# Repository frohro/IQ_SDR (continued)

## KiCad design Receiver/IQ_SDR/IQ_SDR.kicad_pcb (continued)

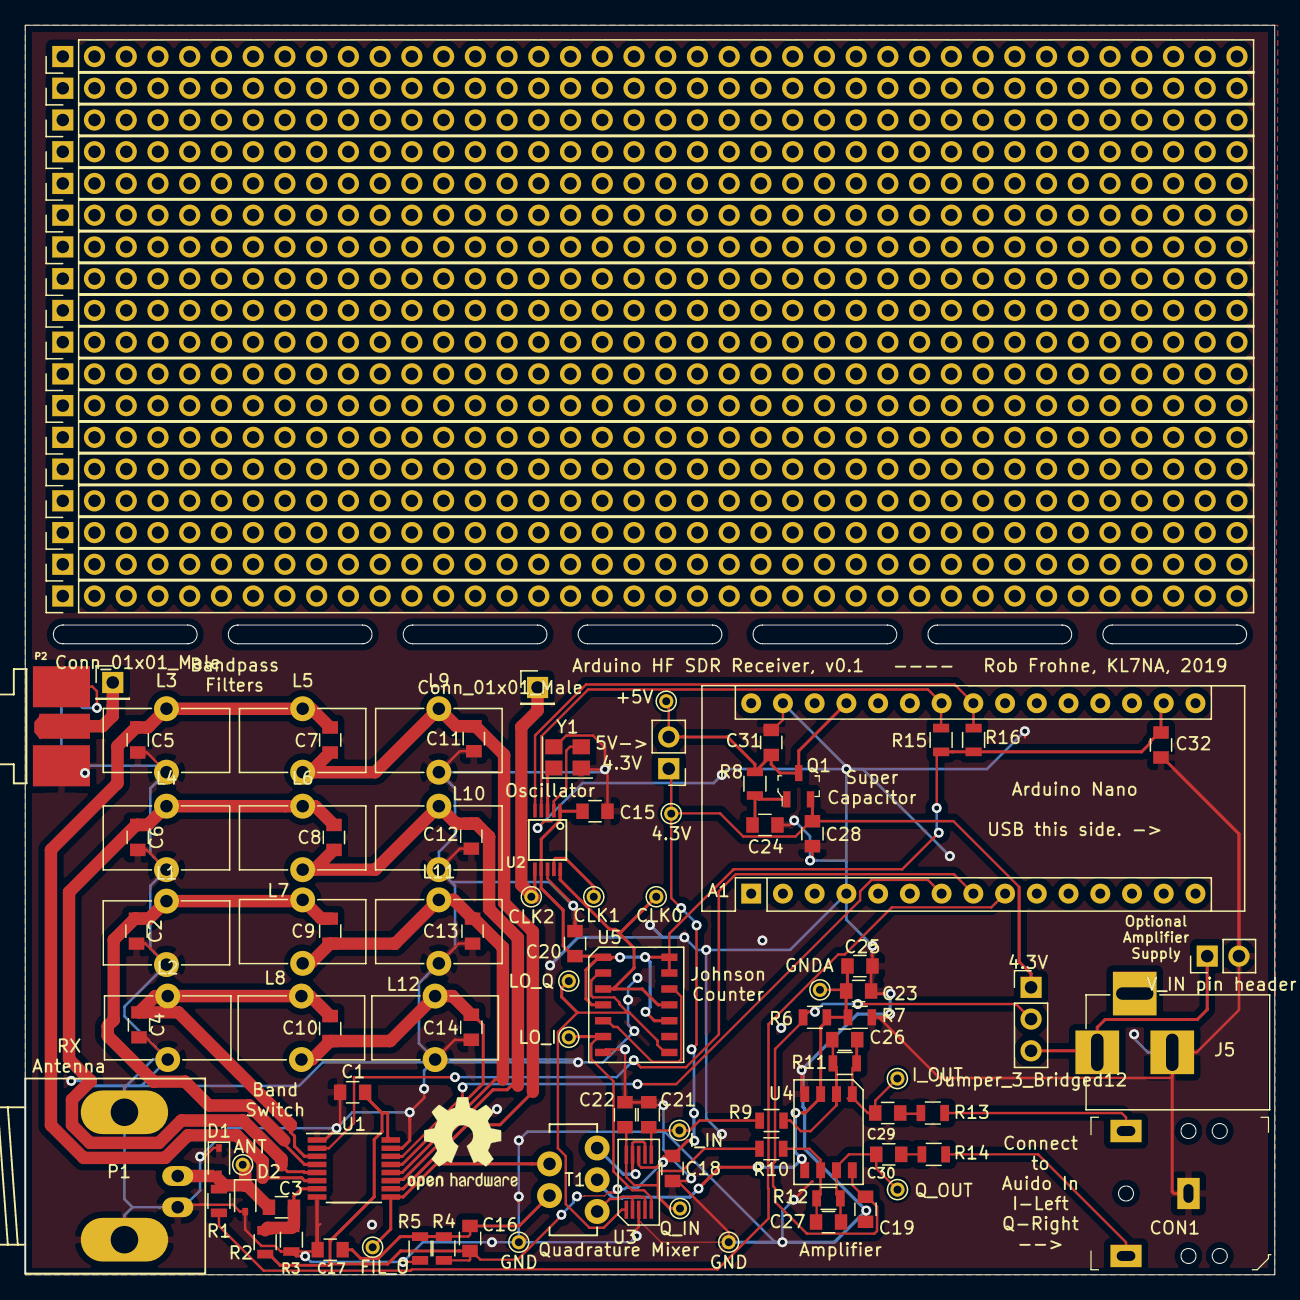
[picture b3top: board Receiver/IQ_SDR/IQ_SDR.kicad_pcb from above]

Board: 2 copper layers, 100.0 x 100.0 mm, 96 parts (0 on the bottom side), 46 nets.

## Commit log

2019-06-06 First commit.
2019-06-07 Fixed schematic issues in Receiver and Transceiver
2019-06-27 Started PI filters.
2019-06-27 Added files .net and .pdf to Receiver
2019-06-28 A little clean up on the schematic
2019-06-28 More cleanup of schematic
2019-07-05 Changes to power and perhaps a better op amp...
2019-07-12 Added PCB.
2019-07-12 ...added the other new kicad files.
2019-09-08 Add inductor/transformer details. Change U1 package type. (Maybe should change the IC as we did in rev 0.1.)
2019-12-15 Added torroid data.
2019-12-17 saving changes so I can merge from hamshack.
2019-12-17 A few more schematic notes from shop.
2019-12-17 Added in changes from the shop after failed merge.
2019-12-17 Fixes to band pass filters, and notes to help with software.
2019-12-26 added rescue libs
2019-12-30 Added notes to schematic about impedance matching.
2019-12-30 added cache.lib
2020-03-23 Fixed R9-R12 and C26 and C26-C27 values
2020-03-25 Added a note of two things to fix
2020-03-29 Added Cern OHL
2020-04-10 Some errors in the bandpass filters and other places corrected to improve the sensitivity and ground loop noise.
2020-04-16 Added the LTSpice simulations and started on v0.20 changes.
2020-04-16 added .gitignore
2020-04-16 removed the output of LTSpice
2020-04-20 Fixed some simulation file errors, especially with the noise simulation.
2020-04-20 rm'ed some simulation files
2020-04-20 rm'ed an unused filter design report
2020-04-20 added better voltage reference for the op amps
2020-04-21 Schematic changes
2020-04-23 Moved the transceiver schematic from Reciever to Transceiver
2020-04-23 Added a few files that were needed for the Kicad in Transceiver
2020-04-24 Schematic modifications for transceiver
2020-04-24 Further change to schematic and moving simulations
2020-04-26 PCB initial design
2020-04-30 More edits to the PCB
2020-04-30 added software for Quisk
2020-04-30 Added arduino stuff
2020-05-07 Commit so I can change branches.
2020-05-07 Corrected some comments on the schematic.
2020-05-07 Added the SDR_Test1 testing program for the Arduino.
2020-05-14 update in libraries for schematic
2020-06-03 Changes after build, mostly with wrong footprints for parts on hand.
2020-06-16 Modified Arduino code for STM32F103C8 (Blue Pill)
2020-07-03 First commit of muSDR receiver
2020-07-03 Fixed submodule config in muSDR branch
2020-07-06 Added U6, finished smoother, tried to fix digikey-kicad-library submodule.
2020-07-06 Added another pair of holes for a band pass filter hack.
2020-07-06 finished footprints and schematic "done"
2020-07-07 Fixed several footprints, and started placing parts....
2020-07-08 Routed PCB for v0.1.
2020-07-08 Created breakout version
2020-07-13 Added libraries needed....
2020-07-13 Added libraries to git repo.
2020-07-13 Added the Transceiver/ cache lib.
2020-07-30 Added notes and C11-C15 value changes.
2020-07-31 changed docs for regulator on schematic
2020-08-04 Changed R18 and R19 to 0 Ohms for better noise performance at the sacrifice of a little DC offset from input bias currents
2020-08-11 Changed the sampling capacitors to 0.01uF for more bandwidth.
2020-08-11 Updated the pdf of the schematic.
2020-09-04 Committing to change to another branch
2021-04-15 Added v0.11 which fixed problems wit stand alone using Nano
2021-04-16 Fixes
2021-04-28 Fixed 3.5mm jack footprints so switched ones will work.
2021-05-24 Updated openradio_quisk.ino to work with v2 of the Si5351 library
2021-06-03 Modifications for quadrature using Si5351
2021-06-03 Added a few prerequisites for building the Arduino code
2021-06-04 Added the ring_buffer back in
2021-06-04 Added PSK.ino
2021-06-06 debugged openradio_quisk.ino for using the SI5351 for both I and Q.
2021-06-07 Removed bogus frequency error in quisk_conf_openradio.py
2022-04-04 So I could change branches.
2022-05-13 Before changing to a new branch.
2022-05-15 Added Raspberry Pi Pico Support with MBED or earlephilhower Arduino development environment.
2022-05-15 Added raspberry pi pico support and quadrature in Si5351
2022-05-16 Added muSDR into the repo. Some notes for changes in the schematic.
2022-05-17 Added frequency correction to New_Quisk_Pico.ino
2022-05-17 Fixed frequency correction bugs.
2022-05-17 Edits to New_Quisk_Pico.ino
2022-05-17 Edited the quisk_conf_openradio.py for two serial ports.
2022-05-18 Changed the feedback resistors and caps for the I&Q channels to tweaked values.
2022-05-21 Fixed a bug for USE_JOHNSON_COUNTER radios (update Si5351 Etherkit library to version 2)
2022-06-10 Added Raspberry Pi Pico support using uSDR-pico since there were problems with the Etherkit si5351 library.
2022-06-22 Tried to add uSDR-pico.
